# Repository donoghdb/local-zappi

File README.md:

# Myenergi Zappi V2.x Local Controller (ESP32-S3)

A dedicated hardware implant for Myenergi Zappi V2.x EV Chargers. This project interfaces directly with the Zappi's internal control bus to provide **Local MQTT**, **Home Assistant**, and **Web Control** without relying on the Myenergi Cloud or Hub. It is intended to action on the 4 external buttons while monitoring the EVSE CP line conversation between the Zappi and the car. It does not affect the software of the Zappi nor does it affect anything else. So it can be removed without affecting anything else.

## ⚠️ DANGER: HIGH VOLTAGE
**This device is installed INSIDE a 240V/400V EV Charger.**
* **Isolate power completely** at the consumer unit/breaker before opening the Zappi.
* High voltage components are centimeters away from the installation area.
* **Use at your own risk.** Improper installation can damage your charger, vehicle, or cause injury.

## 🔌 How It Works
This PCB intercepts the connection between the Zappi **Main Control Board** and the **Front Panel (Display & Buttons)**.

1.  **Power (5V):** Draws power directly from the Zappi's internal 5V rail (no external USB power needed).
2.  **Button Interface:**
    * **Read Mode:** Monitors the 4 physical buttons (Enter, Up, Down, Select) so you can still use the Zappi manually.
    * **Write Mode:** Simulates button presses using Optocouplers/Relays, allowing you to control the menu remotely via WiFi.
3.  **J1772 Pilot Reading:**
    * Taps into the CP (Control Pilot) line to detect accurate Status (A-F) and PWM Duty Cycle (Amps).

## 🛠️ Hardware Interface
The design utilizes an **ESP32-S3-WROOM-1** and integrates via the internal 20-pin Ribbon Header.

| Signal | Function | Connection |
| :--- | :--- | :--- |
| **5V / GND** | Power Supply | Taken from Zappi internal header. |
| **Buttons** | Enter, Up, Down, Select | **Bi-directional:** Reads physical presses & triggers simulated presses via Optocouplers (TCMT4100). |
| **CP Signal** | J1772 State Detection | Read ±12V Pilot Signal. |
| **Boost Relay** | e-Sense Port trigger | Enable via relay. |

### Pinout Configuration (ESP32-S3)
*Based on PCB Revision 1.1*
* **Button Inputs:** GPIO 4, 5, 6, 7
* **Button Triggers:** GPIO 12, 13, 14, 15
* **CP Signal (ADC):** GPIO 8
* **CP Interrupt:** GPIO 3
* **Relay:** GPIO 17

## 💻 Software / Firmware
This project supports two firmware paths depending on your needs:

### Option A: ESPHome (Not complete yet)
Best for **Home Assistant** users. Provides native integration with zero coding.
* Exposes Buttons as simple HA Switches.
* Exposes Charging Amps and State as Sensors.
* **Config:** Copy `esphome/zappi.yaml` and `esphome/zappi_logic.h` to your ESPHome directory.
* Limitations: Does not monitor or track the menu position. The monitoring of the Zappi buttons is not tested yet.

### Option B: Custom C++ Firmware (Best Option)
Best for standalone use or custom MQTT setups.
## 🌟 Features
* **Full Local Control:** No cloud dependency. Works with Home Assistant via MQTT.
* **Offline Scheduler:** Set Start/End times directly on the device via text input (e.g., "07:30"). It handles the mode switching (Stopped ↔ Fast) automatically.
* **Robust Time Sync:**
    * **Primary:** NTP via Google/NIST (Direct IP to bypass DNS issues).
    * **Backup:** "Push" time via MQTT from Home Assistant (works during internet outages).
    * **Safety:** Scheduler only activates once the system year is verified > 2020.
* **Live Monitoring:** View Charging State, Pilot Amps, Duty Cycle, and RSSI.
* **Menu Navigation:** Remotely navigate the Zappi menu using the Web UI or HA.
* **Reliability:** Includes "Last Will & Testament" (LWT) so Home Assistant immediately knows if the device loses power.
* **Others:** Web Interface, WebSocket Live Data, WebSerial, OTA Updates.
* **Tech Stack:** PlatformIO, AsyncWebServer.

## 🔐 Configuration (Custom Firmware)

To keep your WiFi and MQTT passwords safe, this project uses a separate credentials file that is **ignored by Git**.

### 1. Create `src/credentials.cpp`
Create a new file in the `src/` folder named `credentials.cpp` and copy the code below. **Update the values with your actual network details.**

```cpp
#include "credentials.h"
#include <Arduino.h> // for IPAddress

// WiFi Credentials
const char* ssid = "YOUR_WIFI_SSID";
const char* password = "YOUR_WIFI_PASSWORD";

// MQTT Broker Details
const char* mqttServer = "192.168.1.50";
const int mqttPort = 1883;
const char* mqttUser = "homeassistant";
const char* mqttPassword = "mqtt_password";
const char* mqttClientId = "Zappi_Controller";

// Static IP Configuration (Optional)
// Set to 0.0.0.0 if you want to use DHCP
IPAddress staticIP(192, 168, 1, 200);
IPAddress gateway(192, 168, 1, 1);
IPAddress subnet(255, 255, 255, 0);
```

### 2. MQTT Topics
The device uses the base topic `zappi/` (configurable).
* **Controls:** `zappi/button/...`
* **Sensors:** `zappi/sensor/...`
* **Status:** `zappi/status` (online/offline)
* **Scheduler:**
    * Enable: `zappi/switch/zap_sch_en/command` (ON/OFF)
    * Start Time: `zappi/text/zap_sch_start/set` (HH:MM)
    * End Time: `zappi/text/zap_sch_end/set` (HH:MM)
    * Force Time Sync: `zappi/time/set_epoch` (Epoch Timestamp)

## ⚡ Installation (Custom Firmware / PlatformIO)

This method allows you to use the full Web Interface and custom C++ logic.

### 1. Initial Setup (USB)
1.  Clone this repository and open the `firmware_custom` folder in **VS Code** with the **PlatformIO** extension installed.
2.  Connect your ESP32-S3 to your computer via USB.
3.  Open `platformio.ini` and ensure the OTA lines are **commented out** (so it uses USB upload by default):
    ```ini
    ; upload_protocol = espota
    ; upload_port = 192.168.1.X
    ```
4.  Click the **Upload** arrow (→) in the bottom toolbar to flash the firmware.

### 2. Upload the Web Interface (Filesystem)
The HTML files live in a separate partition called LittleFS. You must upload this once, or the web page will be blank.

1.  Click the **PlatformIO Alien Icon** on the left sidebar.
2.  Navigate to: **Project Tasks** → **Platform**.
3.  Click **Upload Filesystem Image**.
4.  Wait for the success message. Your ESP32 will reboot.
5.  The HTML can be updated directly from the webserver later via an Upload page.

### 3. Connect & Use
1.  Search for the WiFi Network: `Zappi-AP` (Password: `password123` or as configured).
2.  Navigate to `http://192.168.4.1` (or the IP assigned by your router).
3.  You should see the Zappi Control Dashboard.

### 4. Future Updates via OTA (Wireless)
Once the device is installed inside the Zappi case, you can update it wirelessly:
1.  Find the IP address of your Zappi Controller (e.g., `192.168.1.50`).
2.  Edit `platformio.ini` and uncomment the OTA lines:
    ```ini
    upload_protocol = espota
    upload_port = 192.168.1.50  ; Replace with your actual IP
    ```
3.  Click **Upload** in PlatformIO. It will now flash over WiFi.

## 🔧 Hardware Installation Guide
1.  **Power Off:** Turn off the Zappi at the breaker.
2.  **Open Case:** Remove the front fascia and unscrew the main cover.
3.  **Locate Header:** Find the 20-pin pin header connecting the main PCB to the screen module.
4.  **Seperate boards:** Use a needle nose pliers to compress each corner connecting pin and carfully seperate the boards.

5.  **Extend Header:** Extend the header using this component Samtec EW-10-12-G-D-250 or this one EW-10-13-G-D-200.
6.  **Connect:** With the extended header connect the boards back together and then attach the ESP32 board.

7.  **Connect CP:** Attach the single sensing wire to the CP terminal block.

8.  **e-Sence:** Attached the 24V output of the zappi power board to the Common Relay connector and the Normally Closed to the e-Sence input on the zappi power board.

9.  **Wifi:** Attach the Zappi existing antenna to the new board or install a new on. Or else create it with this varient ESP32-S3-WROOM-1-N8R2
10.  **Close & Power Up:** Reassemble and restore power.

## 🔌 Schematic

*[Download Full PDF Schematic](docs/local-zappi-power.pdf)*

## 🧩 Bill of Materials (BOM)

This project requires a custom PCB or a perfboard setup designed to fit inside the Zappi case.
There is more Decoupling capacitators than required. Sometimes the power rails dip when the Zappi triggers its own relays. 

### Active Components
| Ref | Component | Description | Notes |
| :--- | :--- | :--- | :--- |
| **U2** | **ESP32-S3-WROOM-1** | MCU Module | Schematic specifies WROOM-1 (PCB Antenna). If using the `1U` version, connect an external IPEX antenna. |
| **U3** | **ADP3338** | 3.3V LDO Regulator | Steps down the Zappi 5V rail to 3.3V for the ESP32. |
| **U1** | **TCMT4100** | Quad Optocoupler | **U1:** Simulates button presses. |

### Passive Components
| Ref | Value | Quantity | Description |
| :--- | :--- | :--- | :--- |
| **R1** | **10kΩ** | 1 | Pull up to 3.3V for ESP32 Enable Pin. |
| **R2-R5** | **39.2Ω** | 4 | Current limiting for Optocoupler LEDs. |
| **R6-R9** | **100Ω** | 4 | Pull/Protection for button return lines. |
| **R10** | **82kΩ** | 1 | Pull up to 3.3V Pilot Signal divider (CP to ADC), 1% Tolerance required. |
| **R11** | **300kΩ** | 1 | High-side Pilot Signal divider (CP to ADC), 1% Tolerance required. |
| **R12** | **100kΩ** | 1 | Low-side Pilot Signal divider (ADC to GND), 1% Tolerance required. |
| **C6, C7, C10, C1, C3** | **10µF** | 4 | Bulk capacitance for LDO & 3.3V Rails. |
| **C2, C4, C8, C11, C12** | **1µF** | 4 | Stability capacitance for LDO. |
| **C5, C9** | **0.1µF** | 2 | Decoupling for ESP32 and Power rails. |

### Connectors
| Component | Quantity | Purpose |
| :--- | :--- | :--- |
| **20-Pin Header** | 1 | 2x10 Samtec (HLE-110-02-L-DV-BE-K-TR) to interface with Zappi mainboard. |
| **2-Pin Terminal** | 1 | Screw terminal for CP (Pilot) wire connection. |
| **3-Pin Header/Terminal** | 1 | Optional Relay/GPIO breakout (JP5). |
| **Buttons** | 2 | Reset and GPIO 0 button. |
| **Mini Relay** | 1 | Optional: Adafruit STEMMA Non-Latching Mini Relay. |

## 🕒 Scheduler & Time Sync
The device includes a **System Time Sensor** (`sensor.system_time`) to show you exactly what time the internal clock thinks it is.

### How it works:
1.  **On Boot:** The device attempts to sync time via NTP using Google & NIST IPs (bypassing local DNS issues).
2.  **Safety Check:** The scheduler **will not run** until the year is > 2020. This prevents the charger from triggering at the wrong time (e.g., 1970).
3.  **Offline Backup:** If your internet is down, Home Assistant can "push" the time to the Zappi via MQTT automation using the topic `zappi/time/set_epoch`.

## 🧪 Testing the CP (Pilot) Signal (Optional Extra if you want to verify the device before installing it)

The Control Pilot (CP) line communicates the state of the EVSE to the car using specific voltage levels (+12V, +9V, +6V) and a 1kHz PWM signal.

Since we are using a **Passive Resistor Divider (300kΩ / 100kΩ)**, it is critical to verify the voltage levels before relying on the automation.

### 1. Bench Testing 
Before installing the unit into the Zappi, you can verify the voltage divider logic using a DC Power Supply or a simple 9V battery.

1.  **Disconnect the ESP32** (if possible) or ensure it is unpowered.
2.  **Apply Voltage** to the CP Terminal on your custom board:
    * **Input 12V:** Measure the voltage at the ESP32 GPIO 8 pin. It should be **~3.0V**.
    * **Input 9V:** Measure the voltage at GPIO 8. It should be **~2.25V**.
3.  **Verify:** If you see >3.3V at the GPIO pin, **STOP**. Your resistor values are incorrect, and you risk frying the ESP32.

### 2. Live Signal Verification
Once installed in the Zappi, use the **WebSerial** (Custom Firmware) or **Home Assistant Logs** (ESPHome) to view the raw ADC readings.

#### Expected ADC Values (12-bit Resolution)
The code looks for the **Peak Voltage** of the signal. Here is what you should see in the logs:

| State | J1772 Voltage | Divider Output | Target ADC Raw |
| :--- | :--- | :--- | :--- |
| **A (Unplugged)** | +12V | ~3.0V | **3600 - 4095** |
| **B (Connected)** | +9V | ~2.25V | **3100 - 3600** |
| **C (Charging)** | +6V (PWM) | ~1.5V | **2500 - 3100** |
| **D (Ventilation)** | +3V (PWM) | ~0.75V | **1900 - 2500** |
| **F (Error/Fault)** | -12V | -3.0V* | **< 1500** |

*> **Note:** The passive divider will pass negative voltages to the GPIO. Ensure your protection diode is in place, or that the ESP32 inputs are clamped effectively to prevent damage during State F.*

### 3. Verifying Amperage (PWM)
When the car enters **State C (Charging)**, the Zappi generates a 1kHz Square Wave.
1.  Check the **"Zappi Duty Cycle"** sensor.
2.  Compare it to the Zappi Screen.
    * **Formula:** `Amps = Duty Cycle x 0.6`
    * *Example:* A 50% Duty Cycle should display as **30A**.

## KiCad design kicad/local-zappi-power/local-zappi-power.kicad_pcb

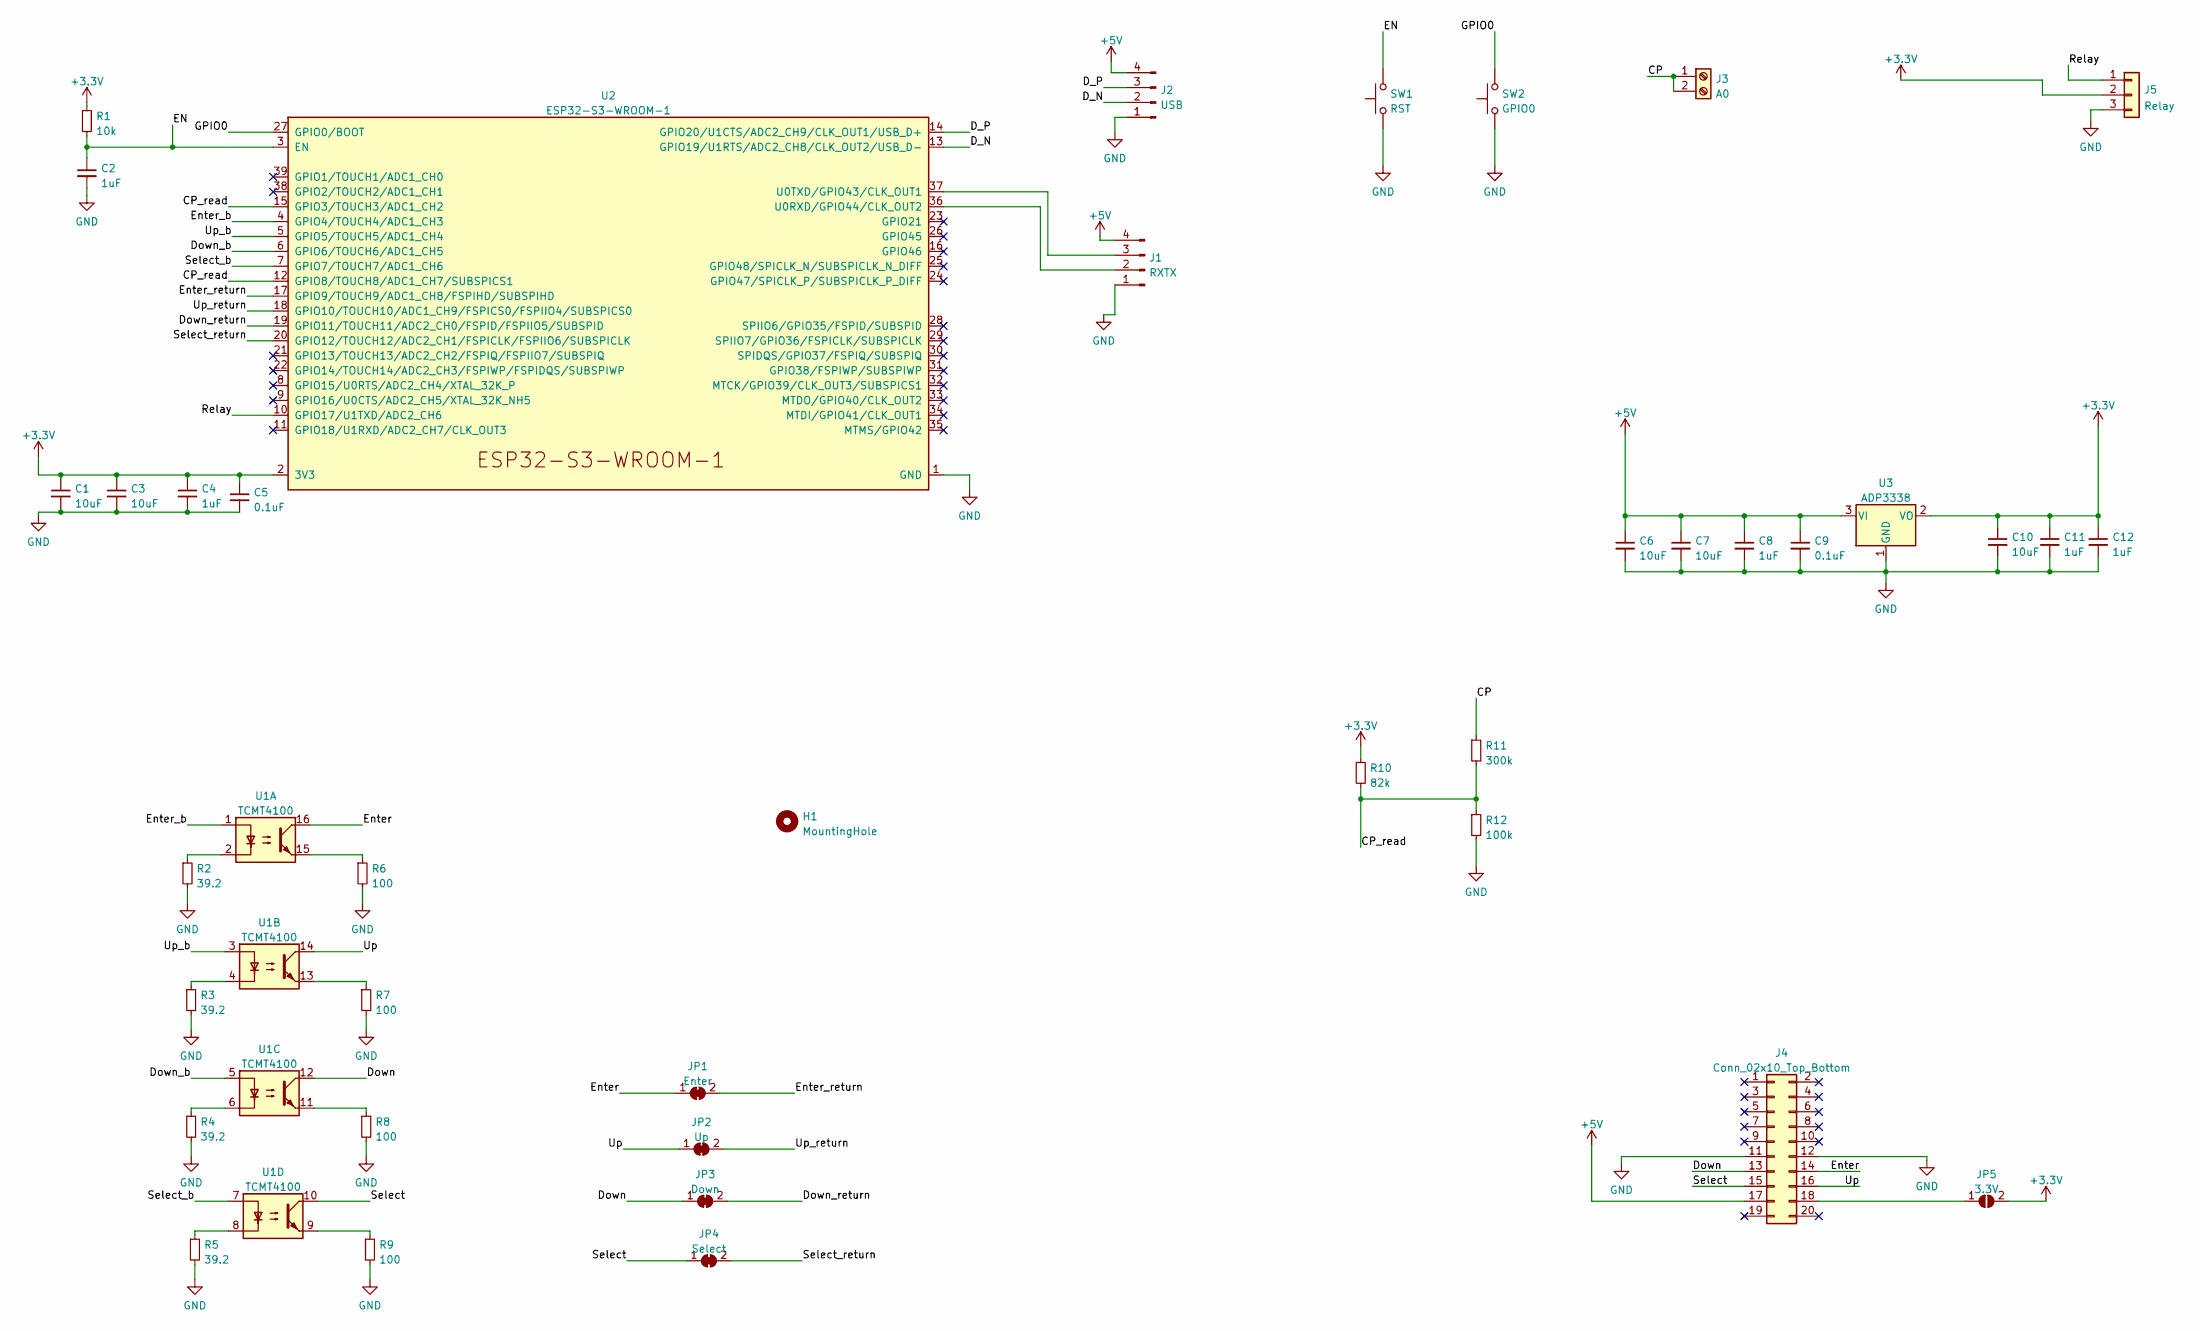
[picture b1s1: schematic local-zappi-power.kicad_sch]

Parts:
C1, C3, C6, C7, C10: 10uF; C_1206_3216Metric_Pad1.33x1.80mm_HandSolder; Mouser GMK316BJ106KL-T
C2, C4, C8, C11, C12: 1uF; C_1206_3216Metric_Pad1.33x1.80mm_HandSolder; Mouser 12065C105K4Z4A
C5, C9: 0.1uF; C_1206_3216Metric_Pad1.33x1.80mm_HandSolder; Mouser 581-KAM31NR72A104KU
H1: MountingHole; MountingHole_2.5mm_Pad_Via
J1: RXTX; PinHeader_1x04_P2.54mm_Vertical
J2: USB; PinHeader_1x04_P2.54mm_Vertical
J3: A0; TerminalBlock_Phoenix_PT-1,5-2-5.0-H_1x02_P5.00mm_Horizontal; Mouser 651-5441537
J4: Conn_02x10_Top_Bottom; Samtec_HLE-110-02-xxx-DV-BE_2x10_P2.54mm_Horizontal
J5: Relay; PinHeader_1x03_P2.54mm_Vertical
JP1: Enter; SolderJumper-2_P1.3mm_Bridged2Bar_Pad1.0x1.5mm
JP2: Up; SolderJumper-2_P1.3mm_Bridged2Bar_Pad1.0x1.5mm
JP3: Down; SolderJumper-2_P1.3mm_Bridged2Bar_Pad1.0x1.5mm
JP4: Select; SolderJumper-2_P1.3mm_Bridged2Bar_Pad1.0x1.5mm
JP5: 3.3V; SolderJumper-2_P1.3mm_Open_TrianglePad1.0x1.5mm
R1: 10k; R_1206_3216Metric_Pad1.30x1.75mm_HandSolder; Mouser CRCW120610K0FKEA
R2, R3, R4, R5: 39.2; R_1206_3216Metric_Pad1.30x1.75mm_HandSolder; Mouser CRCW120639R2FKEAC
R6, R7, R8, R9: 100; R_1206_3216Metric_Pad1.30x1.75mm_HandSolder; Mouser CRCW1206100RJNEA
R10: 82k; R_1206_3216Metric_Pad1.30x1.75mm_HandSolder; Mouser ESR18EZPF8202
R11: 300k; R_1206_3216Metric_Pad1.30x1.75mm_HandSolder; Mouser KTR18EZPF3003
R12: 100k; R_1206_3216Metric_Pad1.30x1.75mm_HandSolder; Mouser CRGP1206F100K
SW1: RST; SW_PUSH_6mm_H4.3mm
SW2: GPIO0; SW_PUSH_6mm_H4.3mm
U1: TCMT4100; SOP-16_4.4x10.4mm_P1.27mm
U2: ESP32-S3-WROOM-1
U3: ADP3338; SOT-223-3_TabPin2; Mouser 584-ADP3338AKCZ3.3R

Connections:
+3.3V: C1.1, C3.1, C4.1, C5.1, C10.1, C11.1, C12.1, J5.2, JP5.2 (B), R1.1, R10.1, U2.2 (3V3), U3.2 (VO)
+5V: C6.1, C7.1, C8.1, C9.1, J1.4, J2.4, J4.17, U3.3 (VI)
/CP: J3.1, J3.2, R11.1
/CP_read: R10.2, R11.2, R12.1, U2.12 (GPIO8/TOUCH8/ADC1_CH7/SUBSPICS1), U2.15 (GPIO3/TOUCH3/ADC1_CH2)
/D_N: J2.2, U2.13 (GPIO19/U1RTS/ADC2_CH8/CLK_OUT2/USB_D-)
/D_P: J2.3, U2.14 (GPIO20/U1CTS/ADC2_CH9/CLK_OUT1/USB_D+)
/Down: J4.13, JP3.1 (A), U1.12
/Down_b: U1.5, U2.6 (GPIO6/TOUCH6/ADC1_CH5)
/Down_return: JP3.2 (B), U2.19 (GPIO11/TOUCH11/ADC2_CH0/FSPID/FSPIIO5/S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)
/EN: C2.1, R1.2, SW1.2, U2.3 (EN)
/Enter: J4.14, JP1.1 (A), U1.16
/Enter_b: U1.1, U2.4 (GPIO4/TOUCH4/ADC1_CH3)
/Enter_return: JP1.2 (B), U2.17 (GPIO9/TOUCH9/ADC1_CH8/FSPIHD/SUBSPIHD)
/GPIO0: SW2.2, U2.27 (GPIO0/BOOT)
/Relay: J5.1, U2.10 (GPIO17/U1TXD/ADC2_CH6)
/Select: J4.15, JP4.1 (A), U1.10
/Select_b: U1.7, U2.7 (GPIO7/TOUCH7/ADC1_CH6)
/Select_return: JP4.2 (B), U2.20 (GPIO12/TOUCH12/ADC2_CH1/FSPICLK/FSPIIO6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)
/Up: J4.16, JP2.1 (A), U1.14
/Up_b: U1.3, U2.5 (GPIO5/TOUCH5/ADC1_CH4)
/Up_return: JP2.2 (B), U2.18 (GPIO10/TOUCH10/ADC1_CH9/FSPICS0/FSPIIO4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)
GND: C1.2, C2.2, C3.2, C4.2, C5.2, C6.2, C7.2, C8.2, C9.2, C10.2, C11.2, C12.2, H1.1, J1.1, J2.1, J4.11, J4.12, J5.3, R2.2, R3.2, R4.2, R5.2, R6.2, R7.2, R8.2, R9.2, R12.2, SW1.1, SW2.1, U2.1 (GND), U2.40 (GND), U2.41 (GND), U3.1 (GND)
unnamed: J1.2, U2.36 (U0RXD/GPIO44/CLK_OUT2)
unnamed: J1.3, U2.37 (U0TXD/GPIO43/CLK_OUT1)
unnamed: J4.18, JP5.1 (A)
unnamed: R2.1, U1.2
unnamed: R3.1, U1.4
unnamed: R4.1, U1.6
unnamed: R5.1, U1.8
unnamed: R6.1, U1.15
unnamed: R7.1, U1.13
unnamed: R8.1, U1.11
unnamed: R9.1, U1.9

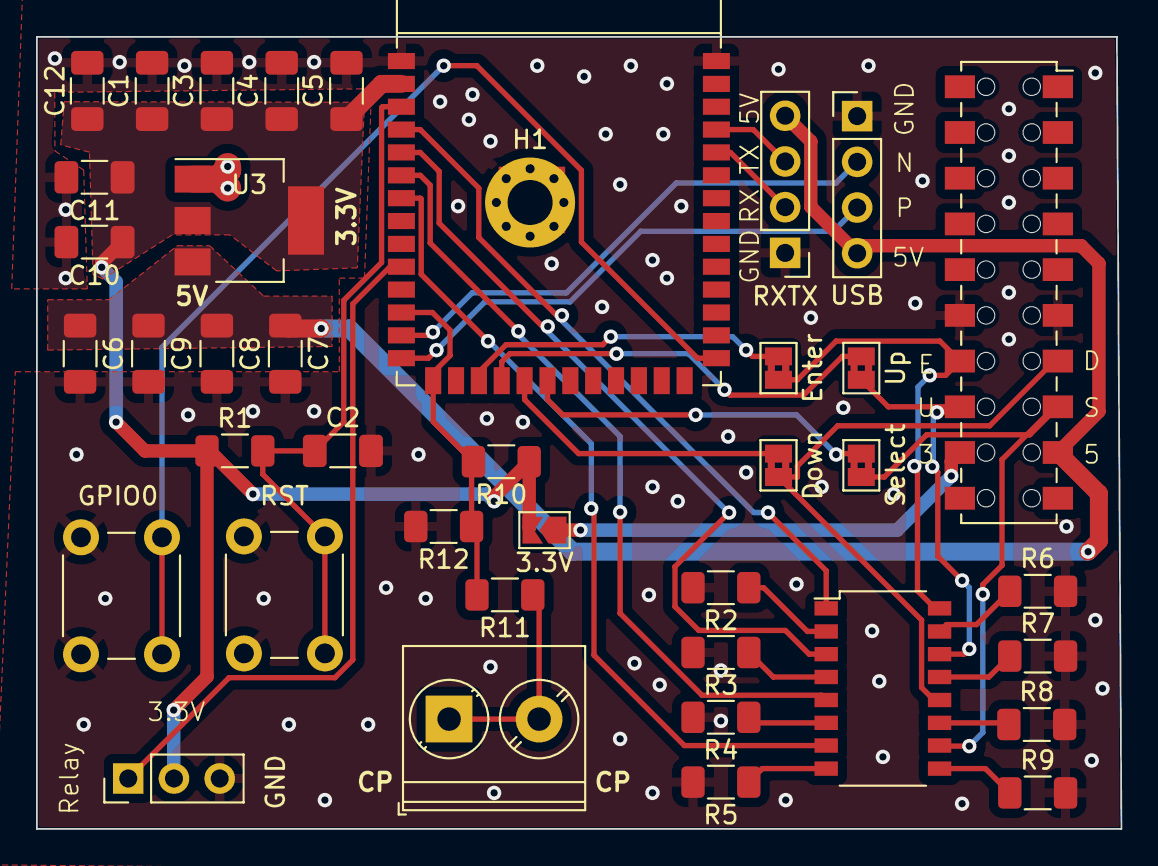
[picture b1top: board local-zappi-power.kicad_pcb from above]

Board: 2 copper layers, 60.2 x 44.0 mm, 40 parts (0 on the bottom side), 33 nets.

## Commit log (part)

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2025-12-16 Initial release
2025-12-16 update formatting
2025-12-23 Swap Switch for Buttons in MQTT
2025-12-26 Update Wifi connection and duty Cycle measurement
2025-12-29 Update for Menu MQTT
2026-01-01 Update menu system
2026-01-02 update entire saving system to match the zappi default Mode when the car is plugged in
2026-01-02 align modes
2026-02-01 added the new Internal Scheduler, Time Sync features, and the Offline Backup capabilities
2026-02-02 stop high current draws during AP scan
2026-02-02 clean up
2026-03-05 Update to allow Fast mode outside of schedule
2026-04-11 Create OTA and AP
2026-04-11 update for dynamic ip
2026-04-11 Mqtt log
